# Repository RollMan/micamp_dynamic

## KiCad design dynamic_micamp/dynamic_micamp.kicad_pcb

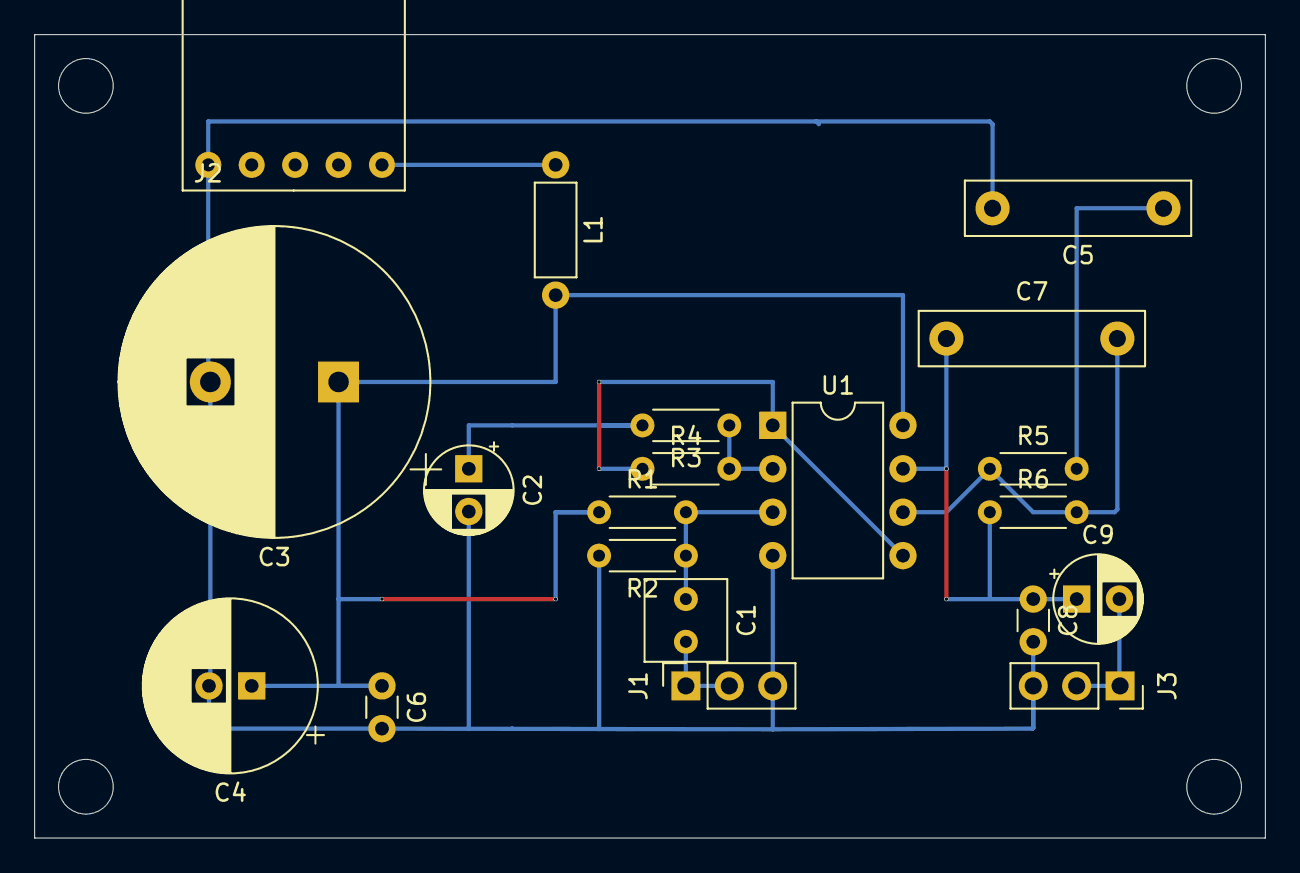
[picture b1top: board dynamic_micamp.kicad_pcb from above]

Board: 2 copper layers, 72.0 x 47.0 mm, 20 parts (0 on the bottom side), 12 nets.

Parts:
C1: 100u; C_Rect_L4.6mm_W4.6mm_P2.50mm_MKS02_FKP02
C2: 10u; CP_Radial_D5.0mm_P2.50mm
C3: 3300u; CP_Radial_D18.0mm_P7.50mm
C4: 470u; CP_Radial_D10.0mm_P2.50mm
C5, C7: 0.1u; C_Rect_L13.0mm_W3.0mm_P10.00mm_FKS3_FKP3_MKS4
C6, C8: 0.1u; C_Disc_D3.0mm_W1.6mm_P2.50mm
C9: 100u; CP_Radial_D5.0mm_P2.50mm
J1, J3: AudioJack3_123; PinSocket_1x03_P2.54mm_Vertical
J2: USB_B_Micro; USB_Micro-B_KOZEEY
L1: 220u; L_Axial_L5.3mm_D2.2mm_P7.62mm_Horizontal_Vishay_IM-1
R1, R2: 100k; R_Axial_DIN0204_L3.6mm_D1.6mm_P5.08mm_Horizontal
R3, R5: 470; R_Axial_DIN0204_L3.6mm_D1.6mm_P5.08mm_Horizontal
R4: 47k; R_Axial_DIN0204_L3.6mm_D1.6mm_P5.08mm_Horizontal
R6: 68k; R_Axial_DIN0204_L3.6mm_D1.6mm_P5.08mm_Horizontal
U1: NJM4580; DIP-8_W7.62mm

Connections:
GND: C2.2, C3.2, C4.2, C5.2, C6.2, C8.2, J1.3, J2.5, J3.3, R2.2, U1.4
unnamed: C1.1, R1.2, R2.1, U1.3
unnamed: C1.2, J1.1, J1.2
unnamed: C2.1, R3.2
unnamed: C5.1, R5.2
unnamed: C7.1, C8.1, C9.1, R6.1, U1.7
unnamed: C7.2, R5.1, R6.2, U1.6
unnamed: C9.2, J3.1, J3.2
unnamed: J2.1, L1.1
unnamed: R3.1, R4.2, U1.2
unnamed: R4.1, U1.1, U1.5
VCC: C3.1, C4.1, C6.1, L1.2, R1.1, U1.8

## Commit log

2020-07-02 constants are fixed using LTSpice simulation
2020-10-15 place footprints
2020-10-15 resize C3 to learger one
2020-10-15 done
